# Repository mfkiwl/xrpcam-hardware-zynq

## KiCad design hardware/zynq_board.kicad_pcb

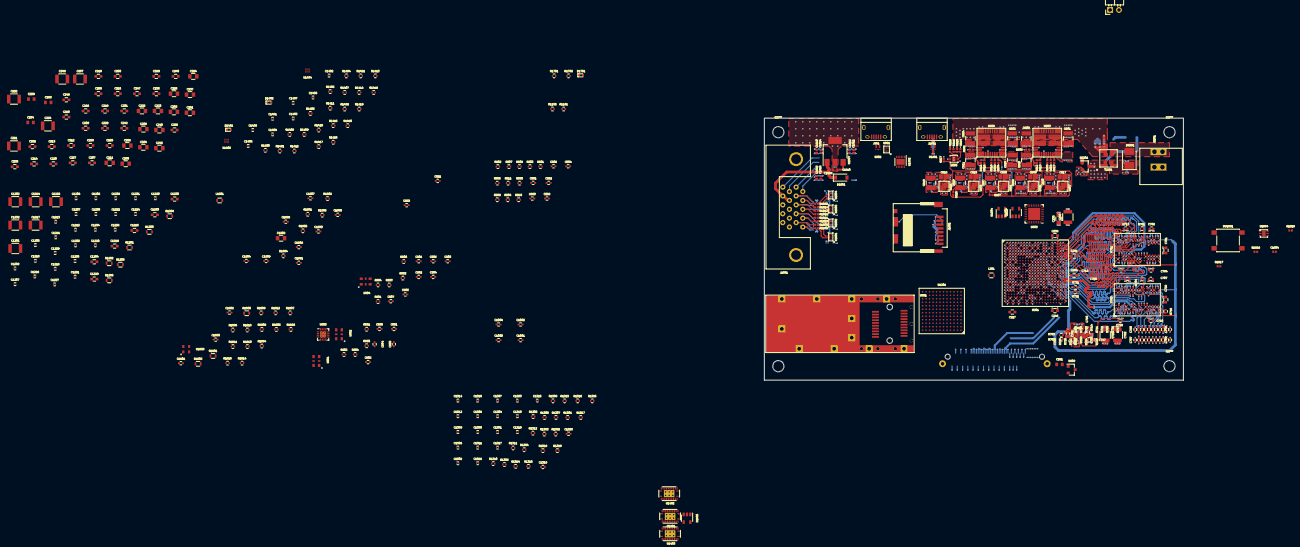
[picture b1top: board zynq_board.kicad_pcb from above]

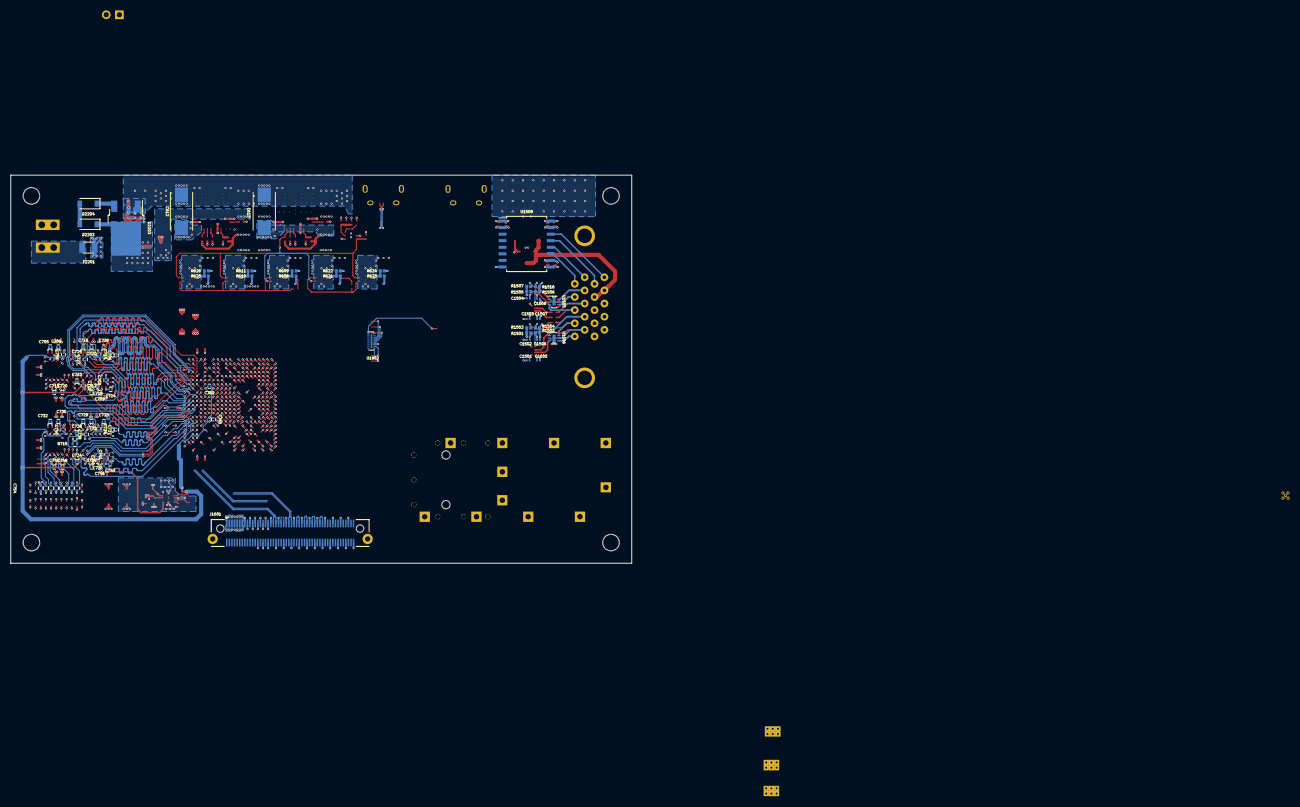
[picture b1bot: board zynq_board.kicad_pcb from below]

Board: 8 copper layers, 120.0 x 75.0 mm, 493 parts (86 on the bottom side), 429 nets.

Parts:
C201, C203, C234, C239: 47µF; C_0603_1608Metric
C204, C205, C206, C208, C211, C223, C224, C225, C226, C236, C237, C243, C245, C251, C256: 4.7µF; C_0805
C207, C221, C222, C232, C248, C254: 100µF; C_1210
C209, C210, C212, C213, C214, C215, C216, C217, C218, C219, C220, C227, C228, C229, C230, C231, C233, C235, C238, C240, C241, C242, C244, C246, C247, C249, C250, C252, C253, C257, C258: 0.47µF; C_0603
C255: 10μF; C_0603
C501, C502, C505, C506: 0.1uF; C_0402
C503, C504: 22uF; C_0402
C601, C602, C603, C604: 10uF 25V; C_1210_3225Metric
C605, C606, C615, C616, C617: 10uF; C_0805_2012Metric
C607, C608, C609, C618, C619, C620: 47uF 6.3V; C_1210_3225Metric
C610, C611: 100uF 6.3V; C_1210_3225Metric
C612, C613: 220uF 6.3V 15mΩ; C7343-31_KEMET-D_10.22x5.6mm
C614, C1804: 1nF; C_0402_1005Metric
C621, C622: 1 µF 6.3 V; C_0402
C701, C728: 10 µF; C_0603
C702, C704, C707, C710, C714, C717, C719, C722: 1µF; C_0402
C703, C705, C706, C708, C709, C711, C712, C713, C715, C716, C718, C720, C721, C723, C724, C725, C726, C727, C729, C730, C731, C732, C733, C734, C735, C736, C737, C738, C739, C740, C741, C742, C743, C744, C746, C748, C749, C1205, C1206, C1207, C1208, C1209, C1210, C1211, C1212, C1213, C1216, C1218, C1220, C1221, C1222, C1223, C1224, C1225, C1227, C1229, C1230, C1231, C1234, C1235, C1236, C1237, C1238, C1301, C1302, C1303, C1304, C1305, C1306, C1307, C1308, C1309, C1310, C1311, C1312, C1313, C1314, C1315, C1316, C1317, C1318, C1401, C1402, C1403, C1404, C1405, C1406, C1407, C1408: 100 nF; C_0201
C745, C756, C761, C762: 0.01µF; C_0201
C747, C750: 10µF; C_0603
C751: 0.22µF; C_0402
C752, C753, C1201, C1202, C1214, C1217, C1226, C1232: 100 µF; C_1210
C754, C755: 4,7 µF; C_0402
C757, C758, C759, C760: 10 nF; C_0201
C801, C802, C803, C804, C902, C904, C905, C906, C907: 100n; C_0402
C805: 1u; C_0402
C901, C903: 2u2; C_0402
C1001, C1002, C1003, C1004: C_Small; C_0402
C1203, C1204, C1215, C1219, C1228, C1233: 4,7 µF; C_0603
C1319, C1320: DNP; C_0402
C1501, C1502, C1503, C1504, C1505, C1506, C1507, C1508, C1512, C1514, C1515: 100 nF; C_0201_0603Metric
C1509, C1510, C1511, C1513, C1516: 1 µF 6,3 V; C_0402_1005Metric
C1801, C1802, C1803, C1904, C1907, C1908, C1909: 100 nF; C_0402
C1901, C1906: 10 nF; C_0402
C1902: 4,7 µF; C_0805
C1903, C1905: 47 pF; C_0402
D1401, D1402: LED_Small; LED_0402
D1501, D2204: PMEG3020EGWX; D_SOD-123
D1701: LED; LED_0402
D2201: P0220SCMCLRP; DO-214AA
D2202: 15 V; D_SOD-123
D2203: TN1515-600B-TR; TO-252-2
F2201: Fuse; Fuse_SMD1206_Reflow
J901, J1901: USB_OTG; USB_Micro-B
J1501: MDR20; Conn_MDR20
J1601: LSHM-150-xxx-x-DV-A-S
J1702: Conn_01x02; Pin_Header_Angled_1x02_Pitch2.54mm
J1801: DM3CS
J2201: Conn_01x02; WAGO-890-802
L201: 120 Ohm @ 1Mhz; L_0603
L1901: 600R@100MHz; L_0603
Q2201: DMP3056L; SOT-23
R501, R503, R504, R506, R507, R508, R509, R903, R1401, R1402, R1403, R1404, R1405, R1406, R1407, R1408, R1409, R1901: 10k; R_0402
R502, R505, R1301, R1303, R1305, R1307, R1309, R1313, R1317, R1701, R1804, R1807, R1809, R1810, R1812: DNP; R_0402
R510, R511, R904, R1418, R1419, R1420, R1421: 1k; R_0402
R601, R602, R603: 31.6k; R_0402_1005Metric
R604: 3.01k; R_0402_1005Metric
R605: 40.2k; R_0402_1005Metric
R606: 124k; R_0402_1005Metric
R607, R616, R617, R620, R627, R1819: 100k; R_0402_1005Metric
R608: 187k 1%; R_0402_1005Metric
R609, R611, R624: 150k 1%; R_0402_1005Metric
R610: 470k 1%; R_0402_1005Metric
R612, R614, R1501, R1503, R1506, R1516: 10k; R_0402_1005Metric
R613: 1.37k; R_0402_1005Metric
R615: 15k; R_0402_1005Metric
R618, R1817: 3M; R_0402_1005Metric
R619: 270k; R_0402_1005Metric
R621: 30k 1%; R_0402_1005Metric
R622: 120k 1%; R_0402_1005Metric
R623: 75k 1%; R_0402_1005Metric
R625: 68k 1%; R_0402_1005Metric
R626: 100k 1%; R_0402_1005Metric
R628: 43k; R_0402_1005Metric
R701, R704: 240Ω; R_0402
R702, R703: 10kΩ; R_0402
R705, R706, R707, R708, R709, R710, R711, R712, R713, R714, R717, R718, R719, R720, R721, R722, R723, R724, R725, R726, R727, R728, R729, R730: 40.2Ω; R_0402
R715, R731, R732: 80.6Ω; R_0402
R716: 4.7 kΩ; R_0402
R801, R802, R803, R901, R1302, R1304, R1306, R1308, R1310: 0; R_0402
R804, R1314: 100; R_0402
R902, R1904, R1905: 100k; R_0402
R905: 8.06k; R_0402
R1101, R1102: 4k7; R_0402
R1201, R1202, R1203, R1204, R1205, R1206: 0; R_0603
R1311, R1315, R1316, R1318, R1319, R1320: R; R_0402
R1312: 2k; R_0402
R1410, R1411: 420; R_0402
R1412, R1413, R1414, R1415: 300; R_0402
R1416, R1417: 200k; R_0402
R1502, R1504, R1505, R1507: DNP; R_0402_1005Metric
R1508, R1509, R1510, R1511, R1512, R1513, R1514, R1515: 270; R_0402_1005Metric
R1702: 430; R_0402
R1801: DNP; R_0603
R1802, R1803: 4k7; R_0603
R1805, R1806, R1808, R1811, R1813, R1814, R1815: 20k; R_0402
R1816: 40,2; R_0402
R1818: 560k; R_0402_1005Metric
R1902, R1903: 27; R_0402
SW1801: SW_Push; SW_SPST_PTS645
T2201: 500 Ohm@100 MHz; DLW5BTM_5.00x5.00mm
U201: xc7z030sbg485; SBG485_22x22_19.0x19.0mm_Pitch0.8mm
U501: SFPP_CONN; SFP+_Connector_with_Cage
U601, U602, U605, U606, U607: TPS8208x; TI_MicroSiP_2.9x3.1mm
U603, U604: TPSM84424; TI_QFM-24_MOL0024A
U608, U1804: TPS3808G01; Texas_S-PWSON-N6
U609: MCP1700-2502E_SOT23; SOT-23
U701, U703: MT41K128M8; BGA-96_2x3x16_9.0x13.0mm_Pitch0.8mm
U702: TPS51206; TI_PWSON-N10_2.0x2.0mm
U801, U802: DIFF_OSC; VDFN_3.2x2.5mm
U803: SI53340; QFN-16-1EP_3x3mm_Pitch0.5mm_ThermalVias
U901: NX5P3090; WLCSP12_3x4_1.35x1.65mm_Pitch0.4mm
U902, U1901: SMP1255PUTG; SMC_MicroDFN_1.8x2.0mm_0.4mm_Pitch
U903: USB3320; QFN-32-1EP_5x5mm_Pitch0.5mm
U904: OSC; VDFN_3.2x2.5mm
U1201: TLK10031; TI-CTR_FCBGA_N144_12x12_13x13mm_Pitch1.0mm
U1401, U1402, U1403: SN74AXC8T245; VQFN-24
U1404, U1405: LSF0102; TI-DQE_PX2SON-N8_1.4x1mm_0.35mm_Pitch
U1501, U1502, U1503, U1504: SN74LVC2T45; DSBGA_2x4_0.918x1.918mm_Pitch0.5mm
U1505, U1506: DMF05LCFLP; DFN-6-1EP_2x2mm_Pitch0.5mm
U1507: TC1262-33; SOT-223
U1508: MAX14854; SOIC-16W_7.5x10.3mm_Pitch1.27mm
U1801: CAT24C02TDI-GT3; SOT-23-5
U1802: EMIF06-MSD02N16; µQFN-16L
U1803: 33.333MHZ; ASDMB_2.5x2.0mm_1.65mm_pitch
U1902: FT234XD; DFN-12-1EP_3x3mm_Pitch0.45mm
U1903, U1904: SN74LV1T126; SOT-23-5

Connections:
+1V0: C205.1, C207.1, C208.1, C210.1, C211.1, C213.1, C215.1, C216.1, C218.1, C219.1, C220.1, C221.1, C224.1, C227.1, C230.1, C610.1, C611.1, C613.1, R614.1, R616.1, R1201.1, R1202.1, R1204.1, R1206.1, U201.G15, U201.H12, U201.H14, U201.J9, U201.J11, U201.J13, U201.J15, U201.K10, U201.L9, U201.L15, U201.M10, U201.N9, U201.N15, U201.P10, U201.R9, U201.R15, U604.1, U604.8
+1V0_MGT: C618.1, R620.1, R621.1, U201.U4, U201.U6, U201.U8, U201.W5, U201.W9, U605.8
+1V2_MGT: C619.1, R623.1, U201.AA2, U201.AA4, U201.AA8, U201.AB1, U201.AB6, U201.V7, U201.Y7, U606.8
+5V: C602.1, C604.1, C605.1, C606.1, C609.1, C612.1, C615.1, C616.1, C617.1, C749.1, C902.1, D1501.2, J1601.1, J1601.3, J1601.5, J1601.7, J1601.9, J1601.11, J1601.13, R612.1, R617.1, R618.1, R628.2, R702.2, R703.1, U601.3, U601.4, U602.3, U602.4, U603.1, U603.8, U604.11, U604.22, U605.3, U605.4, U606.3, U606.4, U607.3, U607.4, U608.1, U702.10, U901.B1, U901.B2, U901.C1
/10G Clock/125_00_MHZ_N: C1003.2, U801.5
/10G Clock/125_00_MHZ_P: C1004.2, U801.4
/10G Clock/156_25_MHZ_0_N: C1001.2, U803.10
/10G Clock/156_25_MHZ_0_P: C1002.2, U803.9
/10G Clock/156_25_MHZ_1_N: C1310.2, U803.12
/10G Clock/156_25_MHZ_1_P: C1305.2, U803.11
/BUTTON0: J1702.1, R1701.2, U201.D6
/Camera Connector/CAM_CLK_0_N: J1601.96, U201.Y15
/Camera Connector/CAM_CLK_0_P: J1601.98, U201.Y14
/Camera Connector/CAM_CLK_1_N: J1601.97, U201.Y19
/Camera Connector/CAM_CLK_1_P: J1601.99, U201.Y18
/Camera Connector/CAM_CTRL_0_N: J1601.36, U201.W16
/Camera Connector/CAM_CTRL_0_P: J1601.38, U201.V16
/Camera Connector/CAM_CTRL_1_N: J1601.63, U201.Y17
/Camera Connector/CAM_CTRL_1_P: J1601.61, U201.W17
/Camera Connector/D0_N: J1601.43, U201.V14
/Camera Connector/D0_P: J1601.45, U201.V13
/Camera Connector/D1_N: J1601.42, U201.W15
/Camera Connector/D1_P: J1601.44, U201.V15
/Camera Connector/D2_N: J1601.54, U201.W13
/Camera Connector/D2_P: J1601.56, U201.W12
/Camera Connector/D3_N: J1601.48, U201.W11
/Camera Connector/D3_P: J1601.50, U201.V11
/Camera Connector/D4_N: J1601.49, U201.U12
/Camera Connector/D4_P: J1601.51, U201.U11
/Camera Connector/D5_N: J1601.55, U201.AB11
/Camera Connector/D5_P: J1601.57, U201.AA11
/Camera Connector/D6_N: J1601.78, U201.AB12
/Camera Connector/D6_P: J1601.80, U201.AA12
/Camera Connector/D7_N: J1601.60, U201.AB14
/Camera Connector/D7_P: J1601.62, U201.AB13
/Camera Connector/D8_N: J1601.72, U201.Y13
/Camera Connector/D8_P: J1601.74, U201.Y12
/Camera Connector/D9_N: J1601.84, U201.AB22
/Camera Connector/D9_P: J1601.86, U201.AB21
/Camera Connector/D10_N: J1601.67, U201.AB19
/Camera Connector/D10_P: J1601.69, U201.AB18
/Camera Connector/D11_N: J1601.73, U201.AB17
/Camera Connector/D11_P: J1601.75, U201.AB16
/Camera Connector/D12_N: J1601.90, U201.AA20
/Camera Connector/D12_P: J1601.92, U201.AA19
/Camera Connector/D13_N: J1601.79, U201.V19
/Camera Connector/D13_P: J1601.81, U201.U19
/Camera Connector/D14_N: J1601.91, U201.W18
/Camera Connector/D14_P: J1601.93, U201.V18
/Camera Connector/D15_N: J1601.85, U201.U18
/Camera Connector/D15_P: J1601.87, U201.U17
/Camera Connector/FRAME_REQ_0: J1601.24, U1402.17
/Camera Connector/FRAME_REQ_1: J1601.18, U1402.20
/Camera Connector/LVDS_CLK0_N: J1601.39, U201.AA15
/Camera Connector/LVDS_CLK0_P: J1601.37, U201.AA14
/Camera Connector/LVDS_CLK1_N: J1601.66, U201.AA17
/Camera Connector/LVDS_CLK1_P: J1601.68, U201.AA16
/Camera Connector/T_EXP1_0: J1601.22, U1402.18
/Camera Connector/T_EXP1_1: J1601.16, U1402.21
/Camera Connector/T_EXP2_0: J1601.20, U1402.19
/Camera Connector/T_EXP2_1: J1601.14, U1401.14
/DDR/A0: R724.2, U201.M19, U701.N3, U703.N3
/DDR/A1: R711.2, U201.M18, U701.P7, U703.P7
/DDR/A2: R723.2, U201.K19, U701.P3, U703.P3
/DDR/A3: R710.2, U201.L19, U701.N2, U703.N2
/DDR/A4: R722.2, U201.K17, U701.P8, U703.P8
/DDR/A5: R709.2, U201.K18, U701.P2, U703.P2
/DDR/A6: R721.2, U201.J16, U701.R8, U703.R8
/DDR/A7: R708.2, U201.J17, U701.R2, U703.R2
/DDR/A8: R720.2, U201.J18, U701.T8, U703.T8
/DDR/A9: R707.2, U201.H18, U701.R3, U703.R3
/DDR/A10: R719.2, U201.J20, U701.L7, U703.L7
/DDR/A11: R706.2, U201.G18, U701.R7, U703.R7
/DDR/A12: R718.2, U201.H19, U701.N7, U703.N7
/DDR/A13: R705.2, U201.F19, U701.T3, U703.T3
/DDR/A14: R717.2, U201.G19, U701.T7, U703.T7
/DDR/DDR_BA0: R730.2, U201.L16, U701.M2, U703.M2
/DDR/DDR_BA1: R714.2, U201.L17, U701.N8, U703.N8
/DDR/DDR_BA2: R729.2, U201.M17, U701.M3, U703.M3
/DDR/DDR_CKE: R727.2, U201.T19, U701.K9, U703.K9
/DDR/DDR_CLK_N: R715.1, U201.N18, U701.K7, U703.K7
/DDR/DDR_CLK_P: R715.2, U201.N19, U701.J7, U703.J7
/DDR/DDR_DM0: U201.B22, U701.E7
/DDR/DDR_DM1: U201.H20, U701.D3
/DDR/DDR_DM2: U201.P22, U703.E7
/DDR/DDR_DM3: U201.AA21, U703.D3
/DDR/DDR_DQS0_N: U201.D21, U701.G3
/DDR/DDR_DQS0_P: U201.C21, U701.F3
/DDR/DDR_DQS1_N: U201.J21, U701.B7
/DDR/DDR_DQS1_P: U201.H21, U701.C7
/DDR/DDR_DQS2_N: U201.P21, U703.G3
/DDR/DDR_DQS2_P: U201.N21, U703.F3
/DDR/DDR_DQS3_N: U201.W21, U703.B7
/DDR/DDR_DQS3_P: U201.V21, U703.C7
/DDR/DDR_ODT: R728.2, U201.P18, U701.K1, U703.K1
/DDR/DQ0: U201.D22, U701.H7
/DDR/DQ1: U201.C20, U701.F7
/DDR/DQ2: U201.B21, U701.F8
/DDR/DQ3: U201.D20, U701.H8
/DDR/DQ4: U201.E20, U701.H3
/DDR/DQ5: U201.E22, U701.E3
/DDR/DQ6: U201.F21, U701.F2
/DDR/DQ7: U201.F22, U701.G2
/DDR/DQ8: U201.G21, U701.D7
/DDR/DQ9: U201.G22, U701.B8
/DDR/DQ10: U201.L22, U701.A3
/DDR/DQ11: U201.L21, U701.A2
/DDR/DQ12: U201.L20, U701.C3
/DDR/DQ13: U201.K22, U701.C2
/DDR/DQ14: U201.J22, U701.A7
/DDR/DQ15: U201.K20, U701.C8
/DDR/DQ16: U201.M22, U703.H8
/DDR/DQ17: U201.T20, U703.H3
/DDR/DQ18: U201.N20, U703.F8
/DDR/DQ19: U201.T22, U703.E3
/DDR/DQ20: U201.R20, U703.G2
/DDR/DQ21: U201.T21, U703.F2
/DDR/DQ22: U201.M21, U703.F7
/DDR/DQ23: U201.R22, U703.H7
/DDR/DQ24: U201.Y20, U703.C2
/DDR/DQ25: U201.U22, U703.D7
/DDR/DQ26: U201.AA22, U703.C3
/DDR/DQ27: U201.U21, U703.B8
/DDR/DQ28: U201.W22, U703.A7
/DDR/DQ29: U201.W20, U703.A3
/DDR/DQ30: U201.V20, U703.C8
/DDR/DQ31: U201.Y22, U703.A2
/DDR/VREF: C745.1, C751.1, C756.1, C761.1, C762.1, U201.H16, U201.P16, U701.H1, U701.M8, U702.6, U703.H1, U703.M8
/DDR/VTT: C750.2, C752.1, C753.1, C754.1, C755.1, C757.1, C758.1, C759.1, C760.1, R705.1, R706.1, R707.1, R708.1, R709.1, R710.1, R711.1, R712.1, R713.1, R714.1, R717.1, R718.1, R719.1, R720.1, R721.1, R722.1, R723.1, R724.1, R725.1, R726.1, R727.1, R728.1, R729.1, R730.1, U702.3, U702.5
/DDR/~DDR_CAS~: R725.2, U201.P20, U701.K3, U703.K3
/DDR/~DDR_CS~: R726.2, U201.P17, U701.L2, U703.L2
/DDR/~DDR_RAS~: R713.2, U201.R18, U701.J3, U703.J3
/DDR/~DDR_RESET~: R716.2, U201.F20, U701.T2, U703.T2
/DDR/~DDR_WE~: R712.2, U201.R19, U701.L3, U703.L3
/IMU_CLK: J1601.19, U201.A7
/IMU_EN_0: J1601.17, U201.B7
/IMU_EN_1: J1601.15, U201.B8
/IMU_FRAME_GPIO0: J1601.25, U201.J5
/IMU_INT1_GPIO1: J1601.27, U201.K5
/IMU_INT2_GPIO2: J1601.29, U201.L5
/IMU_MISO: J1601.23, U201.A6
/IMU_MOSI: J1601.21, U201.B6
/LED1: U201.E8, U1402.8
/LED2: U201.E7, U1402.9
/LS_OK_IN_A: U201.N1, U1201.B10
/LS_OK_OUT_A: U201.P1, U1201.D9
/Levelshifters/CAM0_CLK_REF: J1601.32, U1401.20
/Levelshifters/CAM1_CLK_REF: J1601.28, U1401.21
/Levelshifters/CAM_CLK0_REF_18: U201.B4, U1401.4
/Levelshifters/CAM_CLK1_REF_18: U201.D5, U1401.3
/Levelshifters/CAM_RESET: J1601.2, U1401.19
/Levelshifters/CAM_RESET_18: U201.B3, U1401.5
/Levelshifters/CAM_SCL: J1601.31, R1421.2, U1405.6
/Levelshifters/CAM_SCL_18: R1413.2, U201.A5, U1405.3
/Levelshifters/CAM_SDA: J1601.33, R1419.2, U1405.5
/Levelshifters/CAM_SDA_18: R1415.2, U201.A4, U1405.4
/Levelshifters/CAM_SPI_CLK: J1601.4, U1401.16
/Levelshifters/CAM_SPI_CLK_18: U201.C3, U1401.8
/Levelshifters/CAM_SPI_EN_0: J1601.8, U1401.17
/Levelshifters/CAM_SPI_EN_0_18: U201.A2, U1401.7
/Levelshifters/CAM_SPI_EN_1: J1601.6, U1401.18
/Levelshifters/CAM_SPI_EN_1_18: U201.B2, U1401.6
/Levelshifters/CAM_SPI_MISO: J1601.10, U1403.21
/Levelshifters/CAM_SPI_MISO_18: U201.B1, U1403.3
/Levelshifters/CAM_SPI_MOSI: J1601.12, U1401.15
/Levelshifters/CAM_SPI_MOSI_18: U201.A1, U1401.9
/Levelshifters/FRAME_REQ_0_18: U201.F1, U1402.7
/Levelshifters/FRAME_REQ_1_18: U201.D1, U1402.4
/Levelshifters/MODDET_18: U201.K2, U1403.6
/Levelshifters/RX_LOS_18: U201.J2, U1403.4
/Levelshifters/SFP_GPIO_18: U201.J1, U1403.7
/Levelshifters/SFP_SCL_18: R1412.2, U201.L1, U1404.3
/Levelshifters/SFP_SDA_18: R1414.2, U201.L2, U1404.4
/Levelshifters/TX_DISABLE_18: U201.M1, U1403.8
/Levelshifters/TX_FAULT_18: U201.M2, U1403.5
/Levelshifters/T_EXP1_0_18: U201.E2, U1402.6
/Levelshifters/T_EXP1_1_18: U201.D2, U1402.3
/Levelshifters/T_EXP2_0_18: U201.D3, U1402.5
/Levelshifters/T_EXP2_1_18: U201.C1, U1401.10
/MDC: U201.T1, U1201.J8
/MDIO: R1312.1, U201.T2, U1201.J7
/MODDET: R506.2, U501.6, U1403.18
/PG: R627.2, R1817.1, U201.B18, U602.2, U606.2, U607.2, U608.6
/PL: Bank 34/DE: U201.M3, U1508.6
/PL: Bank 34/RXD: U201.P3, U1508.3
/PL: Bank 34/TXD: U201.K3, U1508.5
/PL: Bank 34/~RE~: U201.N3, U1508.4
/PL: Bank 34/~SBA~: U201.J3, U1508.7
/PL: MGT/MGTX_RX_0_N: C1318.2, U201.AB7
/PL: MGT/MGTX_RX_0_P: C1314.2, U201.AA7
/PL: MGT/MGTX_RX_1_N: C1309.2, U201.Y8
/PL: MGT/MGTX_RX_1_P: C1304.2, U201.W8
/PL: MGT/MGTX_RX_2_N: C1317.2, U201.AB9
/PL: MGT/MGTX_RX_2_P: C1313.2, U201.AA9
/PL: MGT/MGTX_RX_3_N: C1308.2, U201.Y6
/PL: MGT/MGTX_RX_3_P: C1303.2, U201.W6
/PMIC/EN_1V0_MGT: R616.2, U601.1, U604.7, U605.1
/PMIC/EN_1V2_MGT: R620.2, U605.2, U606.1
/PMIC/EN_3V3: R607.2, U601.2, U602.1, U607.1
/PMIC/PG_5V: R617.2, U603.7, U604.10
/PRBSEN: U201.P2, U1201.B9
/Power/VCC_PLL: C255.1, C258.1, L201.2, U201.G13
/Processing System IO/BOOT_MODE[0]: R1806.2, R1807.1, U201.A20
/Processing System IO/BOOT_MODE[1]: R1810.2, R1811.1, U201.F17
/Processing System IO/BOOT_MODE[2]: R1808.2, R1809.1, U201.E19
/Processing System IO/BOOT_MODE[3]: R1812.2, R1813.1, U201.A21
/Processing System IO/BOOT_MODE[4]: R1804.2, R1805.1, U201.A19
/Processing System IO/CLK_33.33: R1816.2, U201.F16
/Processing System IO/PS_RESET: R1819.2, U201.C14, U1804.6
/Processing System IO/SCL: R1803.2, U201.A9, U1801.1
/Processing System IO/SDA: R1802.2, U201.E12, U1801.3
/Processing System IO/SDIO0_CD: J1801.9, U201.D11, U1802.1
/Processing System IO/SDIO0_CK: U201.E9, U1802.6
/Processing System IO/SDIO0_CMD: U201.C15, U1802.5
/Processing System IO/SDIO0_IO0: U201.D15, U1802.7
/Processing System IO/SDIO0_IO1: U201.B12, U1802.8
/Processing System IO/SDIO0_IO2: U201.E10, U1802.3
/Processing System IO/SDIO0_IO3: U201.B14, U1802.4
/Processing System IO/VMODE_0: R1814.1, U201.D18
/Processing System IO/VMODE_1: R1815.1, U201.E18
/RX_LOS: R503.2, U501.8, U1403.20
/SFP_GPIO: R510.1, R511.1, U1403.17
/SFP_SCL: R507.2, R1420.2, U501.5, U1404.6
/SFP_SDA: R508.2, R1418.2, U501.4, U1404.5
/ST: U201.R2, U1201.M9
/TLK10031 Power/DVDD: C1217.1, C1219.1, C1221.1, C1223.1, C1224.1, C1225.1, C1227.1, C1229.1, R1204.2, U1201.D7, U1201.E7, U1201.F7, U1201.G6, U1201.G8, U1201.H7
/TLK10031 Power/VDDA: C1201.1, C1203.1, C1205.1, C1207.1, C1209.1, C1211.1, C1212.1, C1213.1, R1201.2, U1201.D2, U1201.F2, U1201.F11, U1201.G2, U1201.G10, U1201.J2
/TLK10031 Power/VDDD: C1232.1, C1233.1, C1234.1, C1235.1, C1236.1, C1237.1, C1238.1, R1206.2, U1201.E6, U1201.E8, U1201.F6, U1201.H6, U1201.H8
/TLK10031 Power/VDDO: C1226.1, C1228.1, C1230.1, C1231.1, R1205.2, U1201.C7, U1201.K7
/TLK10031 Power/VDDRA: C1214.1, C1215.1, C1216.1, C1218.1, C1220.1, C1222.1, R1203.2, U1201.C3, U1201.E11, U1201.J11, U1201.K3
/TLK10031 Power/VDDT: C1202.1, C1204.1, C1206.1, C1208.1, C1210.1, R1202.2, U1201.F4, U1201.F9, U1201.G4
/TLK10031/HSRXA_N: U501.12, U1201.A12
/TLK10031/HSRXA_P: U501.13, U1201.B12
/TLK10031/HSTXA_N: U501.19, U1201.E12
/TLK10031/HSTXA_P: U501.18, U1201.D12
/TLK10031/INA0_N: C1316.1, U1201.A3
/TLK10031/INA0_P: C1312.1, U1201.A4
/TLK10031/INA1_N: C1307.1, U1201.B1
/TLK10031/INA1_P: C1302.1, U1201.A1
/TLK10031/INA2_N: C1315.1, U1201.C2
/TLK10031/INA2_P: C1311.1, U1201.B2
/TLK10031/INA3_N: C1306.1, U1201.E1
/TLK10031/INA3_P: C1301.1, U1201.D1
/TLK10031/INA[0]_N: C1316.2, U201.AB3
/TLK10031/INA[0]_P: C1312.2, U201.AA3
/TLK10031/INA[1]_N: C1307.2, U201.Y4
/TLK10031/INA[1]_P: C1302.2, U201.W4
/TLK10031/INA[2]_N: C1315.2, U201.AB5
/TLK10031/INA[2]_P: C1311.2, U201.AA5
/TLK10031/INA[3]_N: C1306.2, U201.Y2
/TLK10031/INA[3]_P: C1301.2, U201.W2
/TLK10031/OUTA0_N: C1318.1, U1201.A7
/TLK10031/OUTA0_P: C1314.1, U1201.A6
/TLK10031/OUTA1_N: C1309.1, U1201.B6
/TLK10031/OUTA1_P: C1304.1, U1201.B5
/TLK10031/OUTA2_N: C1317.1, U1201.C5
/TLK10031/OUTA2_P: C1313.1, U1201.C4
/TLK10031/OUTA3_N: C1308.1, U1201.E3
/TLK10031/OUTA3_P: C1303.1, U1201.F3
/TRIG_IN_0: U201.H1, U1501.B1
/TRIG_IN_1: U201.G2, U1501.C1
/TRIG_IN_2: U201.G1, U1502.B1
/TRIG_IN_3: U201.F2, U1502.C1
/TRIG_OUT_0: U201.H4, U1503.B1
/TRIG_OUT_1: U201.G3, U1503.C1
/TRIG_OUT_2: U201.F4, U1504.B1
/TRIG_OUT_3: U201.E3, U1504.C1
/TX_DISABLE: U501.3, U1403.16
/TX_FAULT: R509.2, U501.2, U1403.19
/Triggerbus/3.3V_OUT: C1510.1, J1501.15, J1501.16, U1507.3
/Triggerbus/5V_OUT: C1509.1, D1501.1, J1501.17, J1501.18, U1507.1
/Triggerbus/A: J1501.20, U1508.14
/Triggerbus/B: J1501.19, U1508.13
/Triggerbus/EXT_TRIG_IN_0: J1501.1, R1508.2, U1506.4
/Triggerbus/EXT_TRIG_IN_1: J1501.2, R1509.1, U1506.5
/Triggerbus/EXT_TRIG_IN_2: J1501.3, R1510.2, U1506.6
/Triggerbus/EXT_TRIG_IN_3: J1501.4, R1511.1, U1506.1
/Triggerbus/EXT_TRIG_OUT_0: J1501.5, R1512.2, U1505.3
/Triggerbus/EXT_TRIG_OUT_1: J1501.6, R1513.1, U1505.4
/Triggerbus/EXT_TRIG_OUT_2: J1501.7, R1514.2, U1505.5
/Triggerbus/EXT_TRIG_OUT_3: J1501.8, R1515.1, U1505.6
/Triggerbus/Y: J1501.9, U1508.11
/Triggerbus/Z: J1501.10, U1508.12
/USB-UART/USB_UART_N: C1905.1, J1901.2, R1903.2, U1901.3
/USB-UART/USB_UART_P: C1903.1, J1901.3, R1902.1, U1901.2
/USB-UART/USB_UART_RX: U1902.10, U1904.4
/USB-UART/USB_UART_TX: U1902.7, U1903.2
/USB-UART/VBUS: C1902.1, C1904.1, L1901.2, R1901.1, U1901.1, U1902.4
/USB-UART/VCCIO: C1907.1, C1909.1, R1904.2, U1902.3, U1902.9, U1903.1, U1904.5
/USB/CLK: U201.A14, U903.1
/USB/DATA0: U201.C16, U903.3
/USB/DATA1: U201.G11, U903.4
/USB/DATA2: U201.B11, U903.5
/USB/DATA3: U201.F9, U903.6
/USB/DATA4: U201.A11, U903.7
/USB/DATA5: U201.B9, U903.9
/USB/DATA6: U201.F10, U903.10
/USB/DATA7: U201.C10, U903.13
/USB/DIR: U201.E15, U903.31
/USB/NXT: U201.F14, U903.2
/USB/STP: U201.A12, U903.29
/USB/VBUS_FAULT: R903.2, U901.A2
/V_IN: C601.1, C603.1, Q2201.2, U603.11, U603.22
/~TLK_RESET~: U201.U1, U1201.H5
GND: C201.2, C203.2, C204.2, C205.2, C206.2, C207.2, C208.2, C209.2, C210.2, C211.2, C212.2, C213.2, C214.2, C215.2, C216.2, C217.2, C218.2, C219.2, C220.2, C221.2, C222.2, C223.2, C224.2, C225.2, C226.2, C227.2, C228.2, C229.2, C230.2, C231.2, C232.2, C233.2, C234.2, C235.2, C236.2, C237.2, C238.2, C239.2, C240.2, C241.2, C242.2, C243.2, C244.2, C245.2, C246.2, C247.2, C248.2, C249.2, C250.2, C251.2, C252.2, C253.2, C254.2, C255.2, C256.2, C257.2, C258.2, C501.2, C502.2, C503.2, C504.2, C505.2, C506.2, C601.2, C602.2, C603.2, C604.2, C605.2, C606.2, C607.2, C608.2, C609.2, C610.2, C611.2, C612.2, C613.2, C614.2, C615.2, C616.2, C617.2, C618.2, C619.2, C620.2, C621.2, C622.2, C701.2, C702.2, C703.2, C704.2, C705.2, C706.2, C707.2, C708.2, C709.2, C710.2, C711.2, C712.2, C713.2, C714.2, C715.2, C716.2, C717.2, C718.2, C719.2, C720.2, C721.2, C722.2, C723.2, C724.2, C725.2, C726.2, C727.2, C728.2, C729.2, C730.2, C731.2, C732.2, C733.2, C734.2, C735.2, C736.2, C737.2, C738.2, C739.2, C740.2, C741.2, C742.2, C743.2, C744.2, C745.2, C746.2, C747.2, C748.2, C749.2, C750.1, C751.2, C752.2, C753.2, C754.2, C755.2, C756.2, C757.2, C758.2, C759.2, C760.2, C761.2, C762.2, C801.2, C802.2, C805.2, C901.1, C902.2, C903.2, C904.2, C905.2, C906.2, C907.2, C1201.2, C1202.2, C1203.2, C1204.2, C1205.2, C1206.2, C1207.2, C1208.2, C1209.2, C1210.2, C1211.2, C1212.2, C1213.2, C1214.2, C1215.2, C1216.2, C1217.2, C1218.2, C1219.2, C1220.2, C1221.2, C1222.2, C1223.2, C1224.2, C1225.2, C1226.2, C1227.2, C1228.2, C1229.2, C1230.2, C1231.2, C1232.2, C1233.2, C1234.2, C1235.2, C1236.2, C1237.2, C1238.2, C1401.2, C1402.2, C1403.2, C1404.2, C1405.2, C1406.2, C1407.1, C1408.1, C1501.1, C1502.1, C1503.1, C1504.1, C1505.1, C1506.1, C1507.1, C1508.1, C1509.2, C1510.2, C1511.2, C1512.2, C1513.2, C1514.2, C1515.2, C1516.2, C1801.1, C1802.1, C1803.1, C1804.2, C1901.2, C1902.2, C1903.2, C1904.2, C1905.2, C1906.2, C1907.2, C1908.2, C1909.2, D1401.1, D1402.1, D1701.1, D2203.1, J901.5, J1501.11, J1501.12, J1501.13, J1501.14, J1601.26, J1601.30, J1601.34, J1601.35, J1601.40, J1601.41, J1601.46, J1601.47, J1601.52, J1601.53, J1601.58, J1601.59, J1601.64, J1601.65, J1601.70, J1601.71, J1601.76, J1601.77, J1601.82, J1601.83, J1601.88, J1601.89, J1601.94, J1601.95, J1601.100, J1601.101, J1702.2, J1801.6, J1801.10, J1901.5, J1901.6, Q2201.1, R502.2, R505.2, R601.1, R602.1, R603.2, R604.2, R605.2, R606.2, R609.2, R611.2, R619.2, R622.2, R624.2, R626.2, R701.2, R704.2, R716.1, R732.1, R801.2, R802.2, R901.2, R902.1, R905.1, R1302.2, R1304.2, R1306.2, R1308.2, R1310.2, R1314.2, R1315.1, R1316.1, R1318.1, R1319.1, R1320.1, R1402.1, R1403.1, R1405.1, R1406.1, R1407.1, R1409.1, R1502.2, R1504.2, R1506.2, R1516.2, R1805.2, R1807.2, R1809.2, R1811.2, R1813.2, R1814.2, R1815.2, R1818.2, R1904.1, R1905.2, SW1801.1, T2201.4, U201.A8, U201.A18, U201.AA1, U201.AA6, U201.AA10, U201.AA18, U201.AB2, U201.AB4, U201.AB8, U201.AB10, U201.AB15, U201.B5, U201.B15, U201.C2, U201.C12, U201.C22, U201.D9, U201.D19, U201.E6, U201.E16, U201.F3, U201.F13, U201.G10, U201.G12, U201.G14, U201.G20, U201.H7, U201.H13, U201.H15, U201.H17, U201.J4, U201.J10, U201.J12, U201.J14, U201.K1, U201.K9, U201.K11, U201.K13, U201.K15, U201.K21, U201.L8, U201.L10, U201.L11, U201.L12, U201.L14, U201.L18, U201.M5, U201.M9, U201.M11, U201.M12, U201.M13, U201.M15, U201.N2, U201.N10, U201.N11, U201.N12, U201.N14, U201.N22, U201.P9, U201.P11, U201.P13, U201.P15, U201.P19, U201.R6, U201.R10, U201.R12, U201.R14, U201.R16, U201.T3, U201.T4, U201.T5, U201.T6, U201.T7, U201.T9, U201.T13, U201.U3, U201.U10, U201.U20, U201.V1, U201.V2, U201.V3, U201.V4, U201.V6, U201.V8, U201.V17, U201.W1, U201.W7, U201.W10, U201.W14, U201.Y1, U201.Y3, U201.Y5, U201.Y9, U201.Y10, U201.Y11, U201.Y21, U501.1, U501.10, U501.11, U501.14, U501.17, U501.20, U601.5, U601.6, U601.PAD, U602.5, U602.6, U602.PAD, U603.12, U603.13, U603.14, U603.15, U603.18, U603.19, U603.20, U603.21, U604.12, U604.13, U604.14, U604.15, U604.18, U604.19, U604.20, U604.21, U605.5, U605.6, U605.PAD, U606.5, U606.6, U606.PAD, U607.5, U607.6, U607.PAD, U608.5, U608.7, U609.1, U701.A9, U701.B1, U701.B3, U701.B9, U701.D1, U701.D8, U701.E1, U701.E2, U701.E8, U701.F9, U701.G1, U701.G8, U701.G9, U701.J2, U701.J8, U701.M1, U701.M9, U701.P1, U701.P9, U701.T1, U701.T9, U702.4, U702.8, U702.PAD, U703.A9, U703.B1, U703.B3, U703.B9, U703.D1, U703.D8, U703.E1, U703.E2, U703.E8, U703.F9, U703.G1, U703.G8, U703.G9, U703.J2, U703.J8, U703.M1, U703.M9, U703.P1, U703.P9, U703.T1, U703.T9, U801.3, U802.3, U803.1, U901.B3, U901.C3, U901.D3, U902.5, U902.6, U903.8, U903.14, U904.2, U1201.A2, U1201.A5, U1201.A11, U1201.B3, U1201.B4, U1201.B7, U1201.B11, U1201.C1, U1201.C6, U1201.C12, U1201.D3, U1201.D5, U1201.D10, U1201.D11, U1201.E2, U1201.E4, U1201.E10, U1201.F1, U1201.F5, U1201.F8, U1201.F10, U1201.F12, U1201.G1, U1201.G3, U1201.G5, U1201.G7, U1201.G11, U1201.H1, U1201.H2, U1201.H3, U1201.H4, U1201.H11, U1201.J1, U1201.J3, U1201.J5, U1201.J12, U1201.K1, U1201.K2, U1201.K4, U1201.K5, U1201.K6, U1201.K11, U1201.L1, U1201.L2, U1201.L3, U1201.L4, U1201.L5, U1201.L6, U1201.L7, U1201.L11, U1201.M1, U1201.M2, U1201.M3, U1201.M4, U1201.M5, U1201.M6, U1201.M7, U1201.M12, U1401.12, U1401.13, U1402.12, U1402.13, U1403.12, U1403.13, U1404.1, U1405.1, U1501.D1, U1502.D1, U1503.D1, U1504.D1, U1505.7, U1506.7, U1507.2, U1507.4, U1508.2, U1508.8, U1508.9, U1508.15, U1801.2, U1802.PAD, U1803.2, U1804.5, U1804.7, U1901.5, U1901.6, U1902.5, U1902.13, U1903.3, U1904.3
unnamed: C503.1, C505.1, U501.15
unnamed: C504.1, C506.1, U501.16
unnamed: C614.1, R618.2, R619.1, U608.2
unnamed: C803.1, R804.1, U803.6
unnamed: C803.2, U802.4
unnamed: C804.1, R804.2, U803.7
unnamed: C804.2, U802.5
unnamed: C901.2, J901.1, R904.2, U901.C2, U901.D1, U901.D2, U902.1
unnamed: C1001.1, U201.V9
unnamed: C1002.1, U201.U9
unnamed: C1003.1, U201.V5
unnamed: C1004.1, U201.U5
unnamed: C1305.1, U1201.M10
unnamed: C1310.1, U1201.M11
unnamed: C1319.1, U1201.C9
unnamed: C1319.2, R1313.2
unnamed: C1320.1, U1201.C10
unnamed: C1320.2, R1313.1
unnamed: C1407.2, R1416.2, U1404.7, U1404.8
unnamed: C1408.2, R1417.2, U1405.7, U1405.8
unnamed: C1513.1, C1514.1, U1508.16
unnamed: C1804.1, R1817.2, R1818.1, U1804.2
unnamed: C1901.1, J1901.1, L1901.1
unnamed: C1906.1, R1901.2, U1902.2
unnamed: D1401.2, R1410.1
unnamed: D1402.2, R1411.1
unnamed: D1701.2, R1702.2
unnamed: D2201.1, F2201.1, T2201.2
unnamed: D2201.2, J2201.2, T2201.3
unnamed: D2202.1, D2203.2, Q2201.3, T2201.1
unnamed: D2202.2, D2204.2
unnamed: D2203.3, D2204.1
unnamed: F2201.2, J2201.1
unnamed: J901.2, U902.3, U903.19
unnamed: J901.3, U902.2, U903.18
unnamed: J901.4, U902.4, U903.23
unnamed: J901.6, R901.1
unnamed: R1320.2, U1201.D8
unnamed: J1801.1, U1802.14
unnamed: J1801.2, U1802.13
unnamed: J1801.3, U1802.12
unnamed: J1801.5, U1802.11
unnamed: J1801.7, U1802.10
unnamed: J1801.8, U1802.9
unnamed: J1901.4, U1901.4
unnamed: R501.2, R502.1, R510.2, U501.9
unnamed: R504.2, R505.1, R511.2, U501.7
unnamed: R601.2, U603.6
unnamed: R602.2, U604.6
unnamed: R603.1, U603.5
unnamed: R604.1, U604.5
unnamed: R605.1, U603.24
unnamed: R606.1, U604.24
unnamed: R608.2, R609.1, U601.7
unnamed: R610.2, R611.1, U602.7
unnamed: R612.2, R613.1, U603.2
unnamed: R613.2, U603.3, U603.9, U603.23
unnamed: R614.2, R615.1, U604.2
unnamed: R615.2, U604.3, U604.9, U604.23
unnamed: R621.2, R622.1, U605.7
unnamed: R623.2, R624.1, U606.7
unnamed: R625.2, R626.1, U607.7
unnamed: R628.1, U608.3
unnamed: R701.1, U701.L8
unnamed: R702.1, U702.7
unnamed: R703.2, U702.9
unnamed: R704.1, U703.L8
unnamed: R731.1, U201.M16
unnamed: R732.2, U201.N16
unnamed: R801.1, U803.3
unnamed: R802.1, U803.2
unnamed: R803.1, U803.4
unnamed: R902.2, U901.A3
unnamed: R904.1, U903.22
unnamed: R905.2, U903.24
unnamed: R1101.2, U201.T8
unnamed: R1102.2, U201.V10
unnamed: R1301.2, R1302.1, U1201.H10
unnamed: R1303.2, R1304.1, U1201.G9
unnamed: R1305.2, R1306.1, U1201.L9
unnamed: R1307.2, R1308.1, U1201.J6
unnamed: R1309.2, R1310.1, U1201.M8
unnamed: R1311.1, U1201.A8
unnamed: R1314.1, U1201.K9, U1201.K10
unnamed: R1315.2, R1317.2, U1201.L10
unnamed: R1316.2, U1201.J4
unnamed: R1318.2, U1201.L8
unnamed: R1319.2, U1201.J10
unnamed: R1401.2, U1401.2
unnamed: R1402.2, U1401.11
unnamed: R1403.2, U1401.22
unnamed: R1404.2, U1402.2
unnamed: R1405.2, U1402.11
unnamed: R1406.2, U1402.22
unnamed: R1407.2, U1403.2
unnamed: R1408.2, U1403.11
unnamed: R1409.2, U1403.22
unnamed: R1410.2, U1402.16
unnamed: R1411.2, U1402.15
unnamed: R1501.1, R1502.1, U1501.D2
unnamed: R1503.1, R1504.1, U1502.D2
unnamed: R1505.1, R1506.1, U1503.D2
unnamed: R1507.1, R1516.1, U1504.D2
unnamed: R1508.1, U1501.B2
unnamed: R1509.2, U1501.C2
unnamed: R1510.1, U1502.B2
unnamed: R1511.2, U1502.C2
unnamed: R1512.1, U1503.B2
unnamed: R1513.2, U1503.C2
unnamed: R1514.1, U1504.B2
unnamed: R1515.2, U1504.C2
unnamed: R1801.2, U1801.5
unnamed: R1816.1, U1803.3
unnamed: R1902.2, U1902.12
unnamed: R1903.1, U1902.1
unnamed: SW1801.2, U1804.4
unnamed: U901.A1, U903.17
unnamed: U903.26, U904.3
PS_UART_RX: U201.A16, U1903.4
PS_UART_TX: U201.E13, U1904.2
VCCO_13: C201.1, C204.1, C206.1, C209.1, C212.1, C214.1, C217.1, C622.1, U201.AA13, U201.AB20, U201.T18, U201.U15, U201.V12, U201.W19, U201.Y16, U609.2
VCCO_34: C203.1, C222.1, C223.1, C225.1, C226.1, C228.1, C229.1, C231.1, C233.1, C234.1, C235.1, C237.1, C239.1, C240.1, C242.1, C243.1, C245.1, C247.1, C249.1, C250.1, C252.1, C607.1, C904.1, C905.1, C907.1, C1401.1, C1402.1, C1403.1, C1501.2, C1502.2, C1503.2, C1504.2, C1511.1, C1512.1, L201.1, R607.1, R608.1, R903.1, R1101.1, R1102.1, R1203.1, R1205.1, R1301.1, R1303.1, R1305.1, R1307.1, R1309.1, R1311.2, R1312.2, R1317.1, R1401.1, R1404.1, R1408.1, R1412.1, R1413.1, R1414.1, R1415.1, R1501.2, R1503.2, R1505.2, R1507.2, U201.A3, U201.C7, U201.D4, U201.E1, U201.F8, U201.G5, U201.H2, U201.K6, U201.K12, U201.K14, U201.L3, U201.L13, U201.M14, U201.N7, U201.N13, U201.P4, U201.P12, U201.P14, U201.R1, U201.R11, U201.R13, U201.T11, U201.T12, U201.T14, U201.T15, U601.8, U903.28, U903.30, U904.1, U904.4, U1401.1, U1402.1, U1403.1, U1404.2, U1405.2, U1501.A1, U1502.A1, U1503.A1, U1504.A1, U1508.1
VCCO_DDR: C232.1, C236.1, C238.1, C241.1, C244.1, C246.1, C620.1, C701.1, C702.1, C703.1, C704.1, C705.1, C706.1, C707.1, C708.1, C709.1, C710.1, C711.1, C712.1, C713.1, C714.1, C715.1, C716.1, C717.1, C718.1, C719.1, C720.1, C721.1, C722.1, C723.1, C724.1, C725.1, C726.1, C727.1, C728.1, C729.1, C730.1, C731.1, C732.1, C733.1, C734.1, C735.1, C736.1, C737.1, C738.1, C739.1, C740.1, C741.1, C742.1, C743.1, C744.1, C746.1, C747.1, C748.1, R625.1, R731.2, U201.E21, U201.F18, U201.H22, U201.J19, U201.K16, U201.M20, U201.N17, U201.R21, U201.V22, U607.8, U701.A1, U701.A8, U701.B2, U701.C1, U701.C9, U701.D2, U701.D9, U701.E9, U701.F1, U701.G7, U701.H2, U701.H9, U701.K2, U701.K8, U701.N1, U701.N9, U701.R1, U701.R9, U702.1, U702.2, U703.A1, U703.A8, U703.B2, U703.C1, U703.C9, U703.D2, U703.D9, U703.E9, U703.F1, U703.G7, U703.H2, U703.H9, U703.K2, U703.K8, U703.N1, U703.N9, U703.R1, U703.R9
VCCO_MIO0: C248.1, C251.1, C253.1, C254.1, C256.1, C257.1, C501.1, C502.1, C608.1, C621.1, C801.1, C802.1, C805.1, C903.1, C906.1, C1404.1, C1405.1, C1406.1, C1505.2, C1506.2, C1507.2, C1508.2, C1515.1, C1516.1, C1801.2, C1802.2, C1803.2, C1908.1, J1801.4, R501.1, R503.1, R504.1, R506.1, R507.1, R508.1, R509.1, R610.1, R627.1, R803.2, R1416.1, R1417.1, R1418.1, R1419.1, R1420.1, R1421.1, R1702.1, R1801.1, R1802.1, R1803.1, R1804.1, R1806.1, R1808.1, R1810.1, R1812.1, R1819.1, R1905.1, U201.A13, U201.B10, U201.B20, U201.C17, U201.D14, U201.E11, U602.8, U609.3, U801.6, U802.6, U803.5, U903.11, U903.20, U903.21, U903.32, U1401.23, U1401.24, U1402.23, U1402.24, U1403.23, U1403.24, U1501.A2, U1502.A2, U1503.A2, U1504.A2, U1508.10, U1801.4, U1802.15, U1802.16, U1803.1, U1803.4, U1804.1, U1903.5, U1904.1

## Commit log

2017-07-16 Add first batch of zynq datasheets / app notes
2017-07-18 Add .gitignore with defaults for Linux/OS X/Kicad
2017-07-18 Add very rough schematics outline
2017-07-25 Fill in 10GE interface (WIP)
2017-08-12 Add clocks for 10GE interface
2017-08-12 Add Zynq TRM to datasheets
2018-02-28 Status quo. WIP, no clue about the current status
2018-03-01 Add USB OTG interface
2018-03-01 Connect memory to Zynq (WIP)
2018-03-01 Add SD card and boot config (WIP)
2018-03-04 Fix direction for hierarchical pins
2018-04-02 Add camera connector (WIP)
2018-04-02 Add sheet for Zynq configuration bank 0
2018-04-04 Add symbol for TLK10031
2018-11-18 Change 10GE interface phy to TLK10031
    Low speed signals are still missing. Low speed signals from sfp+ part now need to be connected to the fpga. The new Phy does not support i2c etc..
    Also changed KiCad Version to 4.0.7
2018-11-18 Changed TLK VDDO Voltage to 1V8 and corrected hierachical Pin direction
2018-11-18 Repaired USB OTG Connector
2018-11-18 Added lshm-150 symbol
2018-11-18 Almost drew 3,3 V lowspeed signals. Added Levelshifter Subschematic
    1,8 V Lowspeed Singals from 10 G Phy to FPGA are still missing.
    CAM_REF_CLK is not really low speed, maybe we should consider to use the lvds clock instead. I think it will work, since the signal should be realtive short(FPGA->Connector->Camerasensor[->Camerasens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
    The i2c signals use simple N-Channel MOSTFET Transistors for Levelshifting
2018-11-18 Drew missing 10 G Phy Lowspeed Signals.
    Also moved the SFP+ Lowspeedsignals a bit to ease routing
2018-11-18 Drew Camera Connector part.
    There is some space left on the connector. So it is still possible to add two lvds clocks for the Cameras
2018-11-18 Failed to save Levelshifter Symbol correctly...
2018-11-18 Add all but 7030 supplies. Input protection, connector and some filtering is still missing.
2018-11-18 KiCad does not support differential Busses yet. See https://bugs.launchpad.net/kicad/+bug/1419146. Fixed Data Lanes for Camera Connector.
2018-11-18 Added Symbol for Triggerbus Levelshifter. Triggerbus is WIP
2018-11-18 Moved the FPGAs Memory Port to the DDR Sheet due KiCad 4.0.7 does not support Busses through hiearchical Labels
2018-11-18 Added Second SPI Bus for IMUs to Cam Connector
    This SPI works on 1.8 V, don't confuse them. If this second SPI Bus shall be used for the Cam Chips, add Levelshifters on the Cam Board.
    Also reorderd some stuff around this connector, to ease routing
2018-11-18 Triggerbus WIP.
    Also added more production data
2018-11-18 Finished Triggerbus and added GPIO Header to schematic.
    Also moved some Connections to the FPGA around to hopefully ease routing.
2018-11-18 Added Reset Button, Power LED, 2 Status LEDs and an external Button.
2018-11-18 Added Sdcard Slot.
2018-11-18 Added USB-Uart subschematic. WIP
    USB-Uart will be bus powered. Buffer between FTDI and FPGA is missing.
2018-11-18 Finished USB Uart.
    Also a few more fabrication Informations
2018-11-18 Added decoupling Caps for TLK
2018-11-18 Don't use Global Labels in the DDR Schematic
2018-11-18 Added LDO for Triggerbus.
2018-11-18 Added LVDS Clocks, an second Reference Clock and 3 GPIOs for the IMUs.
    I also tried to beautify the Schematic a little bit.
2018-11-18 Added ESD Protection for microSD Card Slot.
    Also added Fabrication Information to SD-Card Parts and a few Datasheets.
2018-11-18 Added 2 kbit i2c eeprom connected to ps.
2018-11-18 Connect MGT Supplies, POR_B, change reset button, add missing dcm files
2018-11-18 Added a first Version of footprints.
    Some of them are made using the 'kicad footprint generator'-scripting libary. Source code of them is currently not in this repository.
2018-11-18 Changed Camera Connector to be more compatible with the old one. Changing the old Board should now be not a lot of work.
2018-11-18 Connected the Configuration Bank(0).
2018-11-18 Added a few Todos.
2018-11-18 Drew Triggerbus Connector Footprint and Symbol.
2018-11-18 Added decoupling Capacitors for the Zynq. Also added the 2,5 V Power supply.
    The 2,5 V supply was implemented as LDO and is sourced by the 3,3 V Line.
2018-11-18 SD Card Connector Hinge.
2018-11-18 Added Symbol and footprint for lsf0102, added footprint for USB TVS Diode.
2018-11-18 Removed all BSS138PS Transistors due actual unavailability.
    Used lsf0102 as Levelshifter for I2C bus, connected LEDs to already existing Levelshifters.
2018-11-18 First version of Power Input.
2018-11-18 Enhanced Power Connector and Filtering.
    Also added a few more production informations.
2018-11-18 Started to route DDR3 Memory.
    At first added missing Footprint for Reference- and Terminationvoltage Regulator. Added Powerplanes for GND and VCCO. Added decoupling Network to both DDR3 Memory Chips. There are more small caps, to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
2018-11-18 Routed DDR3 Memory. Not length matched yet. Also V_TT and V_Ref is WIP. Changed Footprint for FPGA to match more Xilinx' Specs(and to ease routing).
2018-11-18 Corrected two mistakes in the DDR Sheet. Changed bit sequence a bit to ease routing. Added more decoupling Caps Termination Voltage.
    Mistakes: the Bank Address was not terminated. The Reset Line was connected like it's an terminated Signal. Reset should be connected through an PD Resistor to GND.
2018-11-18 Connected V_TT and V_Ref. Needs to be connected to 5V.
    DDR Traces are still not length matched. V_DDR supply is missing.
2018-11-18 DDR3 Addressbus is length matched.
    Databus is not length matched yet. Also DQS3 still needs to be connected. I have no good Idea for that, yet.
2018-11-18 Length matched DDR3 Traces.
    TODO: evtl. GND Stiching, DDR3 Power, diff. Lane Skew correction.
2018-11-18 Moved the bigger ICs and Connectors to the board to think about placing the connectors.
2018-11-18 Added Power/Protection Circuit
2018-11-18 Length matched DDR3 Memory again.
    Forgot to keep enough space between the traces and between the meander waves.
    Also, I switched to Kicad 5.0 RC2.
    Swaped a few ddr signals.
2018-11-18 Layouted most of the Power Circuit and Triggerbus Levelshifters.
    Added Footprint for Tantal Caps. Modified Footprint for MDR20 Connector, SD-Card.
    Fixed Symbol and Circuit for Power Supervisor/Delay IC.
    Also fixed some smaller things in the schematics.
2018-11-18 Layouted USB-UART.
    Also moved USB-OTG to the right Side of the Board. To get there
    some free Space, i moved the DDR3/Memory and the FPGA a few
    Millimeters down.
2018-11-18 Improved Powerdistribution Network of the FPGA.
    Also started to layout USB.
2018-11-18 Fixed Schematic Symbols
2018-11-18 WIP: TLK Powerdistribution
2018-11-18 Xaui lanes
2018-11-18 SFP+ Power Filter, Levelshifter and MGT/TLK Clock Distribution.
2018-11-18 PS Clock, Reset Button, Cam Levelshifters and big 1.0 V Cap placed.
    Improved some Footprints and library Symbols.
    Also though about Chassis Ground.
2018-11-18 WIP: route GPIOs/Levelshifters
2018-11-18 WIP: routing the HF Part of the Camera Connector. I have to move the clock away from the left border.
    TODO: Fix DDR3 RAM.
2018-11-18 Routed a first Version of the High Speed Part of the Camera Connector. The optional LVDS Clocks are left unconnected. I couldn't keep the Connectors Pin Assignment because it was just impossible to r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
    WIP: general Routing
    Fixed: DDR3 Trace Length Matching
2018-11-18 Added Courtyard to selfmade Footprints. Also general Routing WIP.
2018-11-18 WIP: general Routing
2018-11-18 Routed extra GPIO Solder Pads, reannotated the whole schematic to make it consistent.
    Power Distribution routing WIP
2018-11-18 general routing mainly power distribution, fixed some footprints
2018-11-18 WIP: general routing.
    I got the advice to use at least 125 µm isolation between copper layers in the stackup. This will create the need to change the top/bottom impedance matched traces. This is a TODO
2018-11-18 First Version without any Net not routed.
2018-11-18 Beautified Silkscreen
2019-05-30 Add sym-lib-table and fp-lib-table, fixes for KiCad 5
2019-05-31 Added Step Models, fixed some footprints(e.g. added solderpaste), cleaned up a bit
